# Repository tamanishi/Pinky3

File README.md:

# Pinky3

> **Warning**  
> If you are using Kicad 6, please see https://github.com/tamanishi/Pinky4/issues/4 .

A split 3 x 7 vertically staggered keys and 4 thumb keys keyboard.  
An idea is inspired from [crkbd](https://github.com/foostan/crkbd), [Lily58](https://github.com/kata0510/Lily58), [Ergo42](https://github.com/Biacco42/Ergo42) and [Helix](https://github.com/MakotoKurauchi/helix).  

## Pcb & Plates

<!--  -->

## Bill of Materials (for both hands)

| # | name | qty |
| ---: | :--- | ---: |
| 1 | pcbs | 2 |
| 2 | top plates | 2 |
| 3 | bottom plates | 2 |
| 4 | Pro Micros | 2 |
| 5 | Conthrough for Pro Micros | 4 |
| 6 | 2 pins tact switches | 2 |
| 7 | TRRS connectors | 2 |
| 8 | diodes (1N4148 or 1N4148W) | 50 |
| 9 | Kailh PCB Sockets (MX Sockets) | 42 |
| 10 | Kailh PCB Sockets (Choc Sockets) | 8 |
| 11 | Cherry MX compatible keyswitches | 42 |
| 12 | Kailh low profile (Choc) keyswitches | 8 |
| 13 | Cherry MX compatible keycaps | 42 |
| 14 | Kailh low profile (Choc) compatible keycaps | 8 |
| 15 | TRS or TRRS cable | 1 |
| 16 | 7mm M2 standoffs (for top and bottom plates) | 10 |
| 17 | 5.5mm M2 standoffs (for Pro Micro cover plates) | 4 |
| 18 | 4mm M2 screws | 28 |
| 19 | rubber cushions | 8 |

## Firmware

See [Quantum Mechanical Keyboard Firmware](https://qmk.fm) and [its Pinky support page](https://github.com/qmk/qmk_firmware/blob/master/keyboards/pinky/readme.md)

## TODOs

- [x] add images (finished product, pcb, plates and parts?)
- [x] add BOM
- [ ] add build log

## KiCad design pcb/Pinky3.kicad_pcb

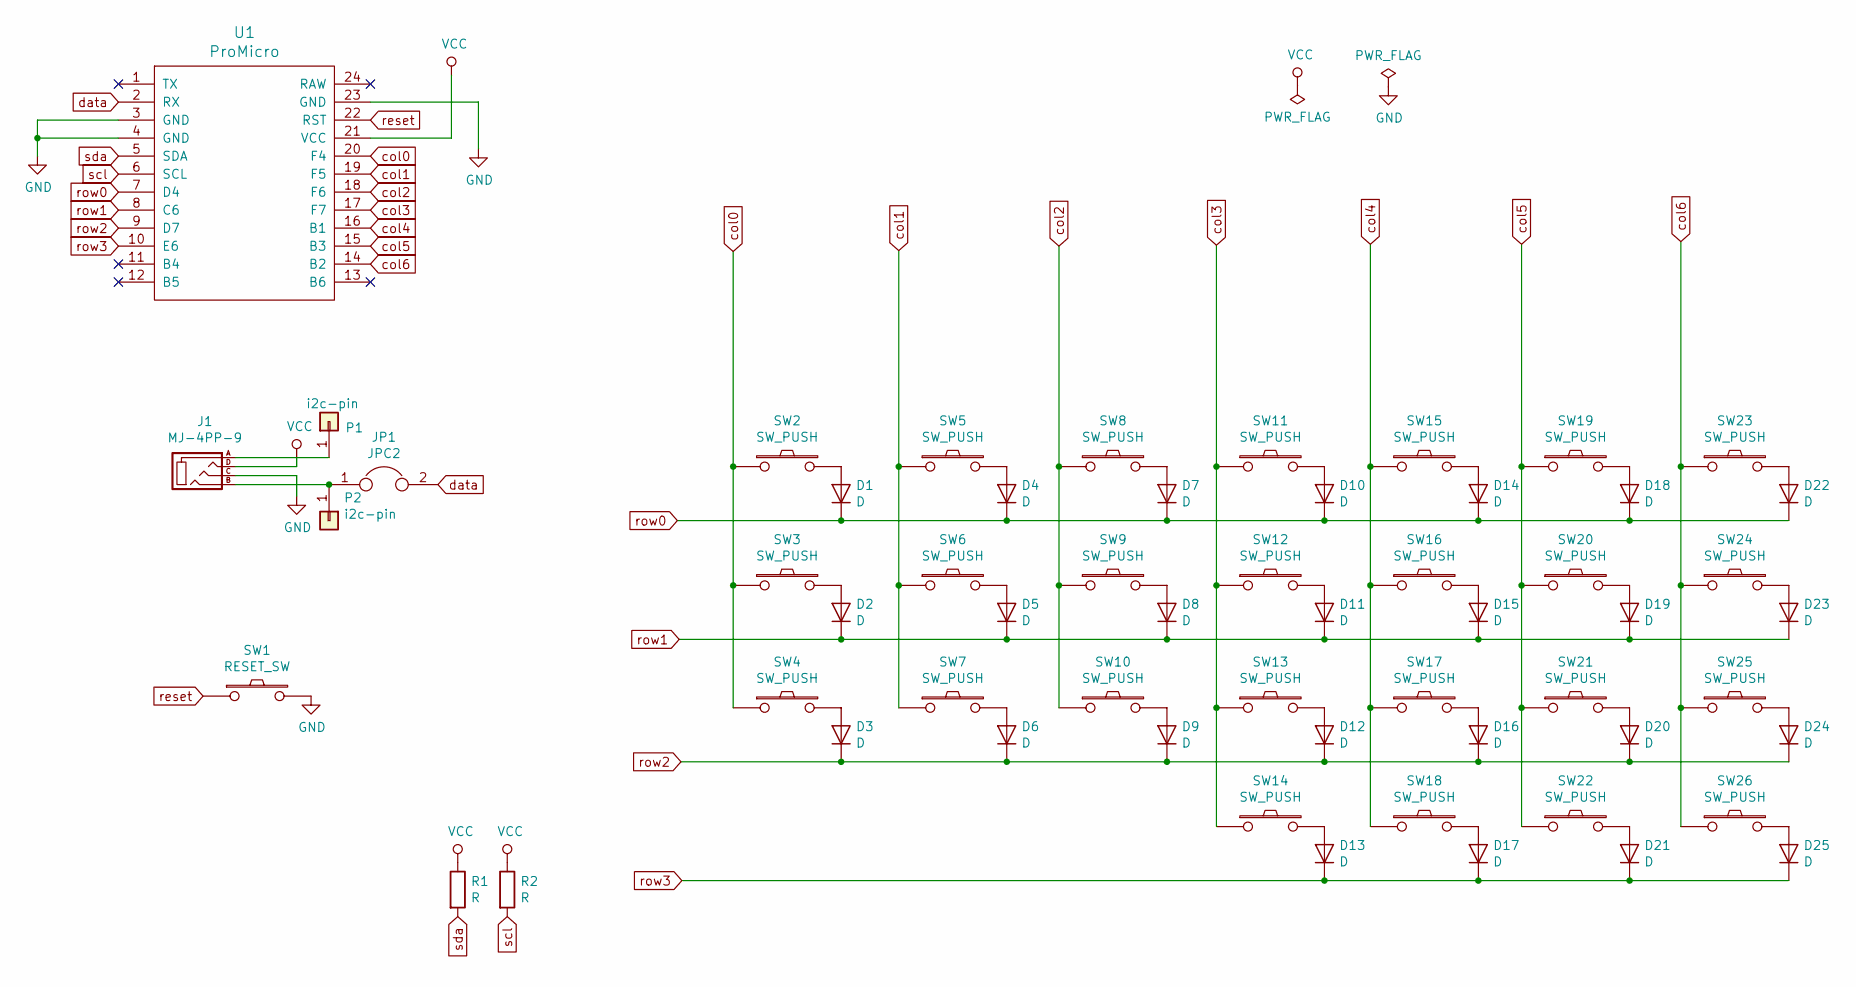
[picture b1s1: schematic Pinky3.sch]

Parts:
D1, D2, D3, D4, D5, D6, D7, D8, D9, D10, D11, D12, D13, D14, D15, D16, D17, D18, D19, D20, D21, D22, D23, D24, D25: D; D3_TH_SMD
J1: MJ-4PP-9
JP1: JPC2
P1, P2: i2c-pin; 1pin_conn
R1, R2: R
SW1: RESET_SW; ResetSW
SW2, SW3, SW4, SW5, SW6, SW7, SW8, SW9, SW10, SW11, SW12, SW13, SW15, SW16, SW17, SW19, SW20, SW21, SW23, SW24, SW25: SW_PUSH; CherryMX_Hotswap
SW14, SW18, SW22, SW26: SW_PUSH; Choc_Hotswap
U1: ProMicro; ProMicro_v2

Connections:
GND: J1.C, SW1.2, U1.3 (GND), U1.4 (GND), U1.23 (GND)
unnamed: D1.2 (A), SW2.2
unnamed: D2.2 (A), SW3.2
unnamed: D3.2 (A), SW4.2
unnamed: D4.2 (A), SW5.2
unnamed: D5.2 (A), SW6.2
unnamed: D6.2 (A), SW7.2
unnamed: D7.2 (A), SW8.2
unnamed: D8.2 (A), SW9.2
unnamed: D9.2 (A), SW10.2
unnamed: D10.2 (A), SW11.2
unnamed: D11.2 (A), SW12.2
unnamed: D12.2 (A), SW13.2
unnamed: D13.2 (A), SW14.2
unnamed: D14.2 (A), SW15.2
unnamed: D15.2 (A), SW16.2
unnamed: D16.2 (A), SW17.2
unnamed: D17.2 (A), SW18.2
unnamed: D18.2 (A), SW19.2
unnamed: D19.2 (A), SW20.2
unnamed: D20.2 (A), SW21.2
unnamed: D21.2 (A), SW22.2
unnamed: D22.2 (A), SW23.2
unnamed: D23.2 (A), SW24.2
unnamed: D24.2 (A), SW25.2
unnamed: D25.2 (A), SW26.2
unnamed: J1.B, JP1.1, P2.1
col0: SW2.1, SW3.1, SW4.1, U1.20 (F4)
col1: SW5.1, SW6.1, SW7.1, U1.19 (F5)
col2: SW8.1, SW9.1, SW10.1, U1.18 (F6)
col3: SW11.1, SW12.1, SW13.1, SW14.1, U1.17 (F7)
col4: SW15.1, SW16.1, SW17.1, SW18.1, U1.16 (B1)
col5: SW19.1, SW20.1, SW21.1, SW22.1, U1.15 (B3)
col6: SW23.1, SW24.1, SW25.1, SW26.1, U1.14 (B2)
data: JP1.2, U1.2 (RX)
reset: SW1.1, U1.22 (RST)
row0: D1.1 (K), D4.1 (K), D7.1 (K), D10.1 (K), D14.1 (K), D18.1 (K), D22.1 (K), U1.7 (D4)
row1: D2.1 (K), D5.1 (K), D8.1 (K), D11.1 (K), D15.1 (K), D19.1 (K), D23.1 (K), U1.8 (C6)
row2: D3.1 (K), D6.1 (K), D9.1 (K), D12.1 (K), D16.1 (K), D20.1 (K), D24.1 (K), U1.9 (D7)
row3: D13.1 (K), D17.1 (K), D21.1 (K), D25.1 (K), U1.10 (E6)
scl: R2.2, U1.6 (SCL)
sda: R1.2, U1.5 (SDA)

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
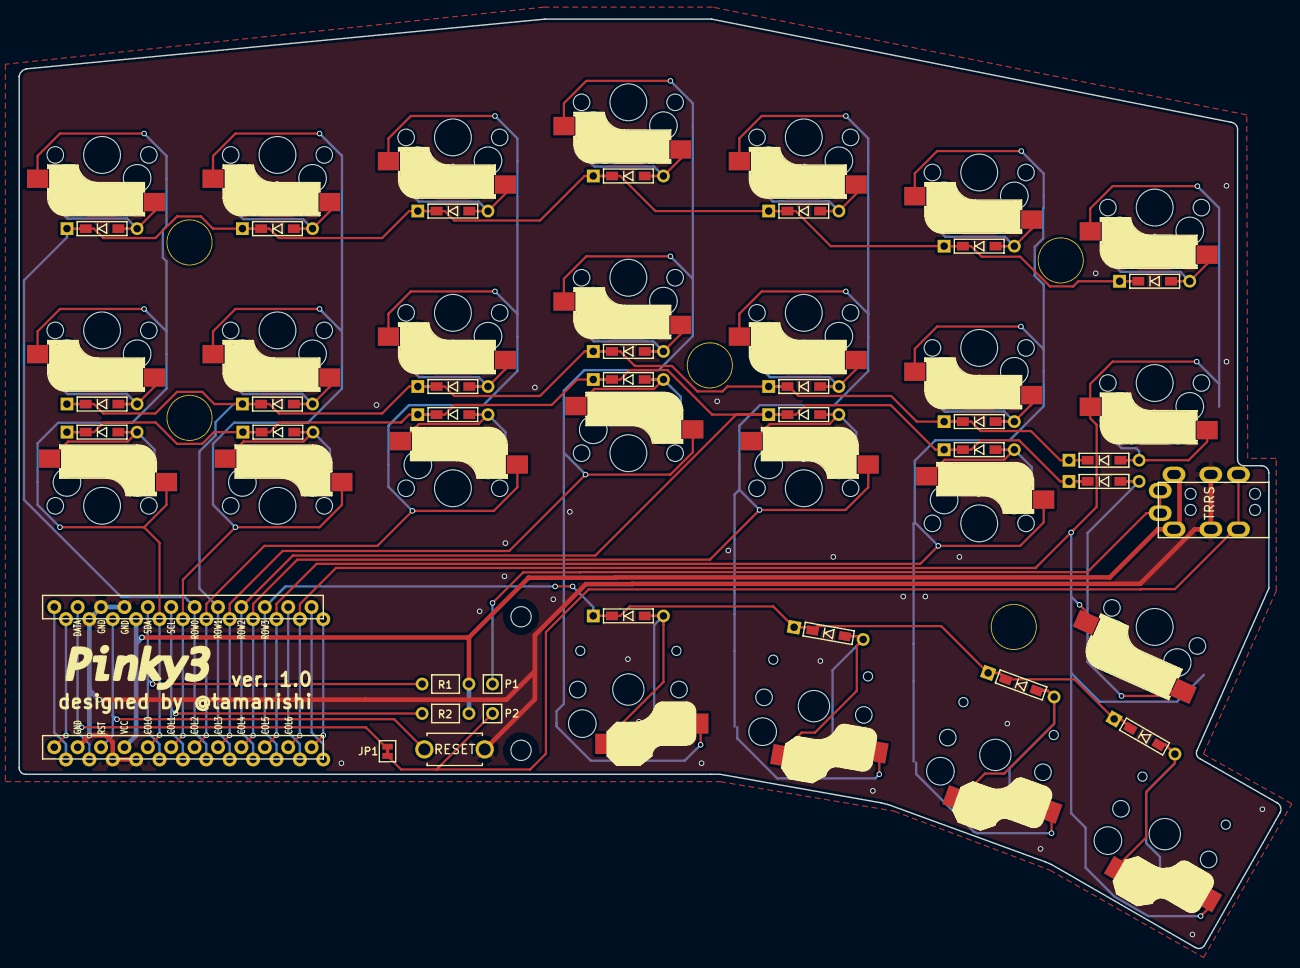
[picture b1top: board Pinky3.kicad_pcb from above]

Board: 2 copper layers, 137.0 x 100.9 mm, 65 parts (0 on the bottom side), 44 nets.

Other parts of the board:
HOLE_M2, HOLE_M2#2: VAL**; HOLE_M2
Ref**: Val**; HOLE
Ref**#2, Ref**#3, Ref**#4, Ref**#5: Val**; HOLE

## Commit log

2018-12-23 tweak
2018-12-28 readme
2019-01-06 - add images - add logo - change thumb keys footprints to choc only
2019-01-06 maintain README.md
2019-01-14 add BOM
2019-01-14 - join plates - tweak README
2019-01-14 fixed qty
2019-01-15 remove joined plate
2019-01-15 join plates
2019-01-20 change production image.
2019-01-23 replace I and U
2019-08-16 add top plate only project
2019-09-03 create branch
2019-09-04 [WIP] worked for Choc and XSwitch PCB design
2019-09-05 prototype pcb ordered
2019-09-07 maintain README
2019-09-07 tweak README.md
2019-09-07 tweak row2
2019-10-06 tweak silk
2019-10-06 add photo
2019-10-06 add Thanks
2019-12-07 add plates dxf.
2019-12-18 add plate DXF
2020-01-12 - change thumb switches to Kailh PG1232.
2020-02-24 PG1232
2020-02-24 add Horizontal Reset Switch
2020-04-05 supports choc v2
2020-04-05 change horizontal reset switch
2020-07-27 tweak standoff length for cover plates
2021-05-08 maintenance
